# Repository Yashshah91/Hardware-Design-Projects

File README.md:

# 🔧 Electronics & Embedded Systems Projects  

Welcome to my collection of electronics, embedded systems, and power electronics projects.  
This repository contains hardware designs, schematics, and code implementations for robotics, microcontrollers, power supplies, and circuit testing solutions.  

---

## 📂 Project Index  

### 🤖 Robotics & Control  
- **[01_Robotics_Controller_4Axis](./01_Robotics_Controller_4Axis)**  
  A 4-axis robotics controller designed for precision motor control and automation tasks.  

### 🔬 Microcontroller Boards  
- **[02_ATmega128A_DevBoard](./02_ATmega128A_DevBoard)**  
  Custom development board based on the ATmega128A microcontroller for embedded applications.  

### ⚡ Power Electronics  
- **[03_Power_Solutions_Shared](./03_Power_Solutions_Shared)**  
  A collection of shared power solutions for multiple projects.  
- **[05_12V-10A-Power-Supply-Circuit](./05_12V-10A-Power-Supply-Circuit)**  
  A high-current regulated power supply circuit (12V, 10A).  
- **[06_Battery_Charger_and_Protection](./06_Battery_Charger_and_Protection)**  
  Battery charging and protection circuit ensuring safe operation for lithium-based batteries.  

### 🧪 Circuit Testers  
- **[04_555-Tester](./04_555-Tester)**  
  A tester circuit for the popular NE555 timer IC.  

---

## 🚀 Getting Started  

Each project folder contains:  
- ✅ Circuit diagrams / schematics  
- ✅ PCB layouts (if applicable)  
- ✅ Source code / firmware (for microcontroller-based designs)  
- ✅ Documentation & notes

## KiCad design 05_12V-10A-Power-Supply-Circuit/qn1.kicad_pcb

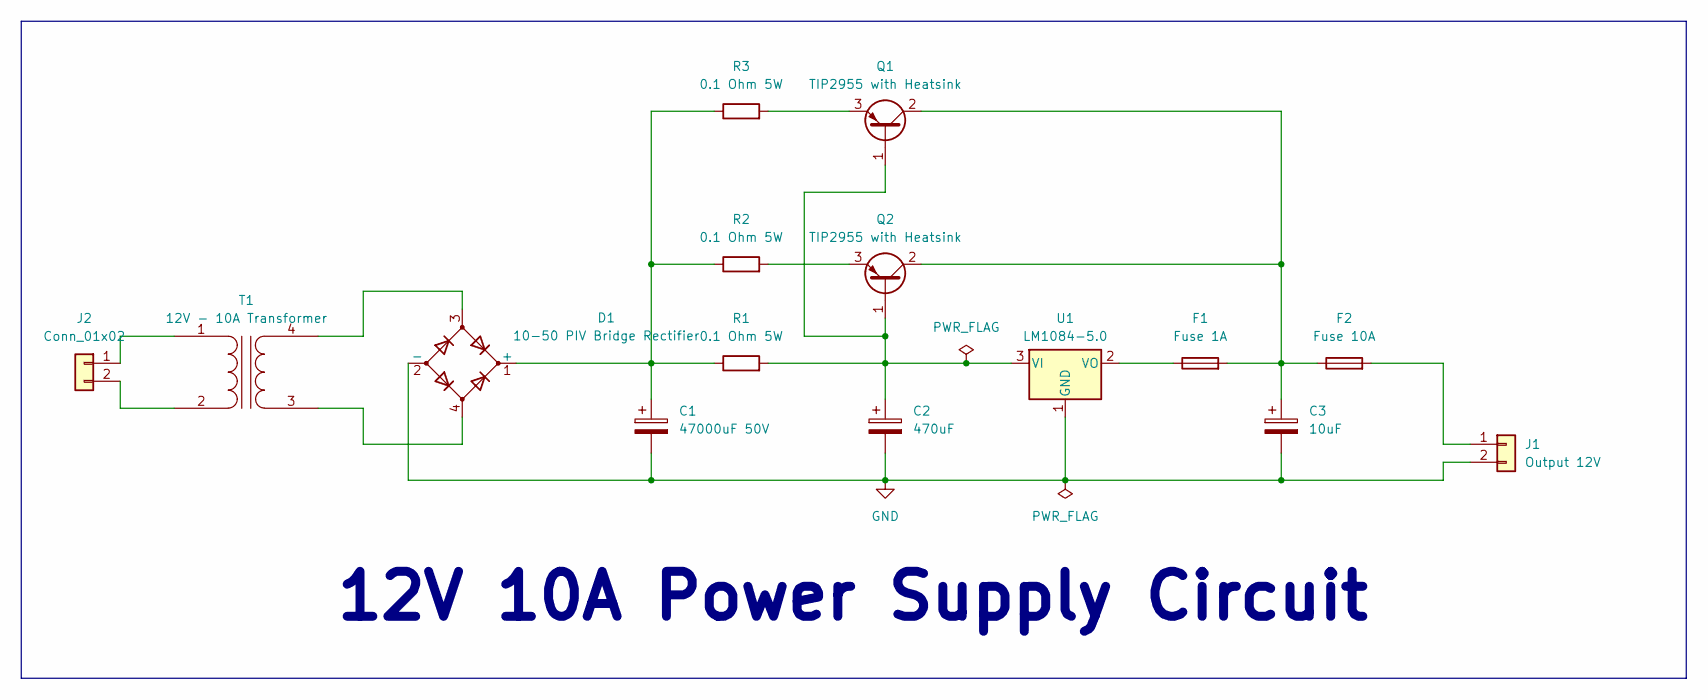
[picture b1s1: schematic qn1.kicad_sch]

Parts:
C1: 47000uF 50V; C_Radial_D16.0mm_H25.0mm_P7.50mm
C2: 470uF; C_Radial_D10.0mm_H12.5mm_P5.00mm
C3: 10uF; C_Radial_D5.0mm_H11.0mm_P2.00mm
D1: 10-50 PIV Bridge Rectifier; DIP-4_W7.62mm
F1: Fuse 1A; Fuse_BelFuse_0ZRE0150FF_L23.4mm_W5.3mm
F2: Fuse 10A; Fuse_BelFuse_0ZRE0150FF_L23.4mm_W5.3mm
J1: Output 12V; PinHeader_1x02_P2.54mm_Vertical
J2: Conn_01x02; PinHeader_1x02_P2.54mm_Vertical
Q1, Q2: TIP2955 with Heatsink; TO-218-3_Vertical
R1, R2, R3: 0.1 Ohm 5W; R_Axial_DIN0207_L6.3mm_D2.5mm_P7.62mm_Horizontal
T1: 12V - 10A Transformer; Transformer_CHK_EI54-12VA_1xSec
U1: LM1084-5.0; TO-220-3_Vertical

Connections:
GND: C1.2, C2.2, C3.2, D1.2 (-), J1.2, U1.1 (GND)
unnamed: C1.1, D1.1 (+), R1.1, R2.1, R3.1
unnamed: F2.2, J1.1
unnamed: J2.1, T1.1 (AA)
unnamed: J2.2, T1.2 (AB)
unnamed: C2.1, Q1.1 (B), Q2.1 (B), R1.2, U1.3 (VI)
unnamed: C3.1, F1.2, F2.1, Q1.2 (C), Q2.2 (C)
unnamed: Q1.3 (E), R3.2
unnamed: Q2.3 (E), R2.2
unnamed: D1.4, T1.3 (SA)
unnamed: D1.3, T1.4 (SB)
unnamed: F1.1, U1.2 (VO)

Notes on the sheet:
12V 10A Power Supply Circuit

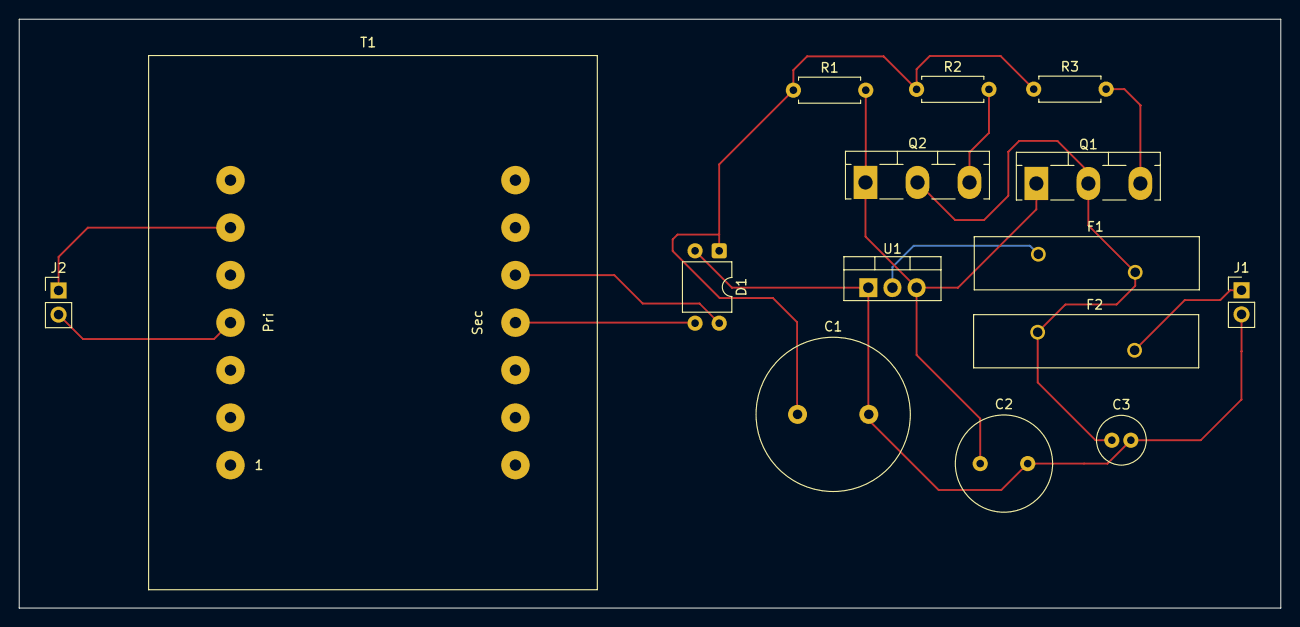
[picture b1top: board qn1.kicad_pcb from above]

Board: 2 copper layers, 132.8 x 62.0 mm, 15 parts (0 on the bottom side), 12 nets.

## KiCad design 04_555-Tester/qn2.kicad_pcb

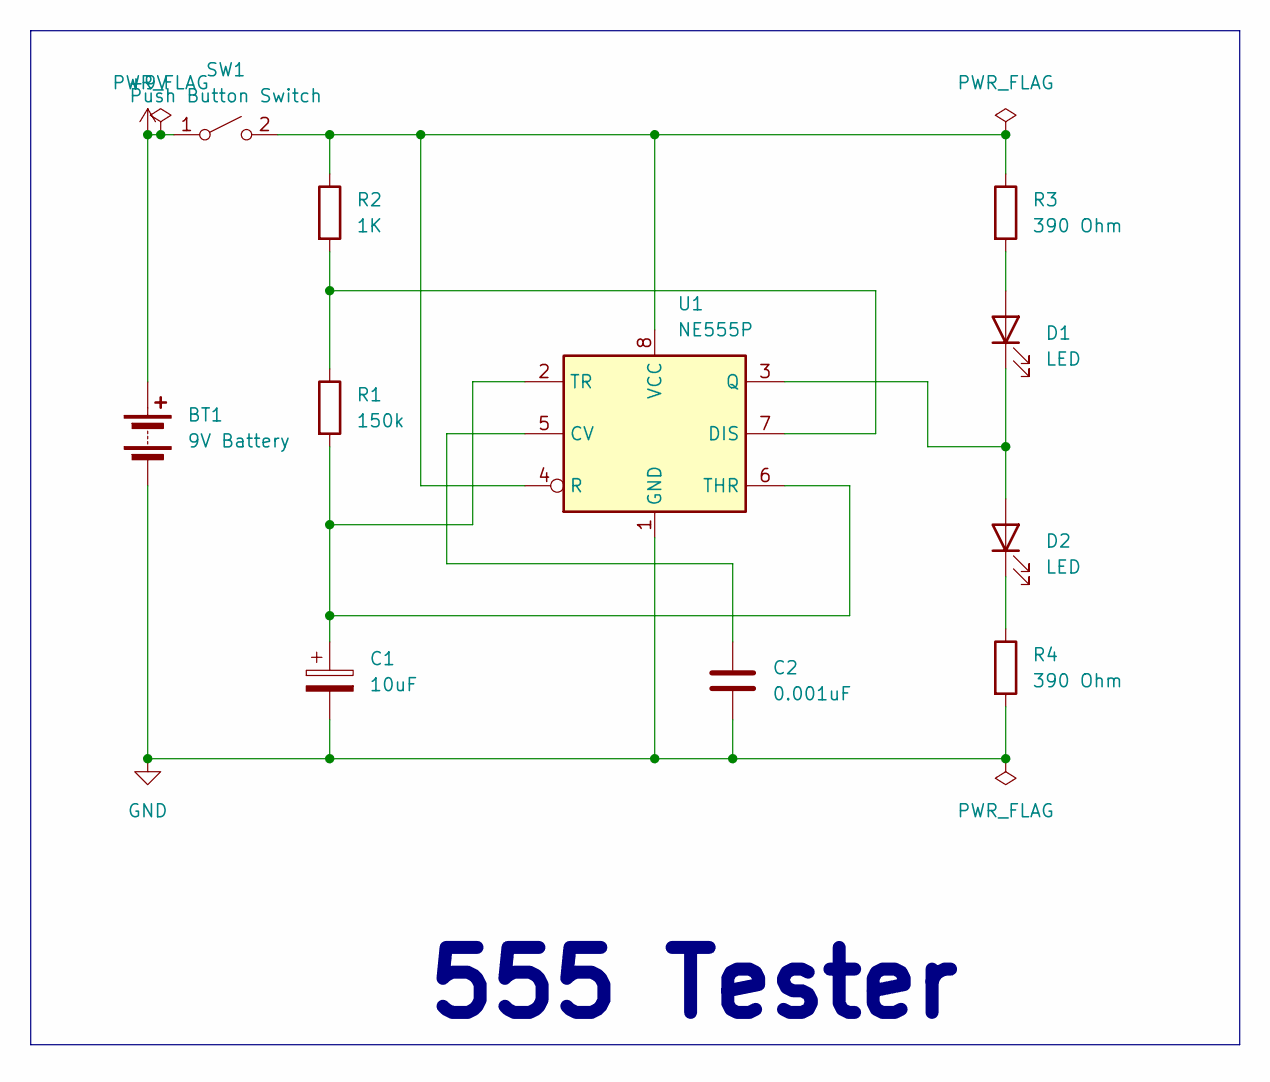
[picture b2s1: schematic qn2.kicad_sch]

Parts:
BT1: 9V Battery; BatteryHolder_Keystone_2462_2xAA
C1: 10uF; CP_Radial_D10.0mm_P7.50mm
C2: 0.001uF; CP_Axial_L10.0mm_D4.5mm_P15.00mm_Horizontal
D1, D2: LED; LED_D3.0mm
R1: 150k; R_Axial_DIN0207_L6.3mm_D2.5mm_P7.62mm_Horizontal
R2: 1K; R_Axial_DIN0207_L6.3mm_D2.5mm_P7.62mm_Horizontal
R3, R4: 390 Ohm; R_Axial_DIN0207_L6.3mm_D2.5mm_P7.62mm_Horizontal
SW1: Push Button Switch; SW_CW_GPTS203211B
U1: NE555P; DIP-8_W7.62mm

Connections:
+9V: BT1.1 (+), SW1.1 (A)
GND: BT1.2 (-), C1.2, C2.2, R4.2, U1.1 (GND)
unnamed: D1.2 (A), R3.2
unnamed: D1.1 (K), D2.2 (A), U1.3 (Q)
unnamed: D2.1 (K), R4.1
unnamed: R2.1, R3.1, SW1.2 (B), U1.4 (R), U1.8 (VCC)
unnamed: C2.1, U1.5 (CV)
unnamed: R1.1, R2.2, U1.7 (DIS)
unnamed: C1.1, R1.2, U1.2 (TR), U1.6 (THR)

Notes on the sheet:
555 Tester

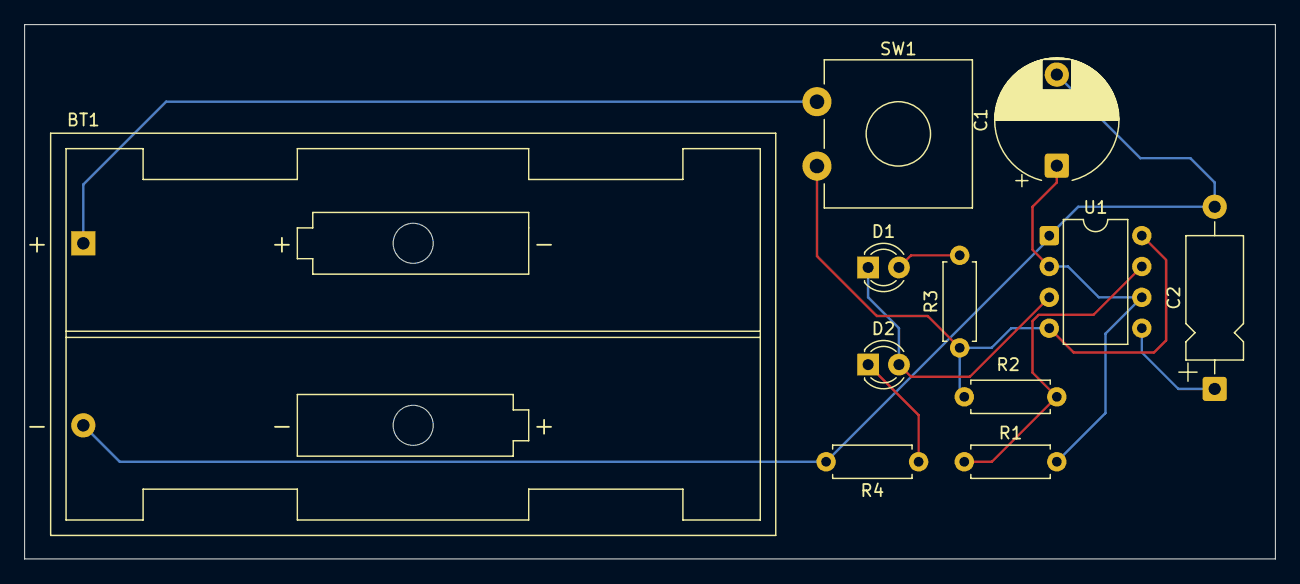
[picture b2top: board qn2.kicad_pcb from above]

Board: 2 copper layers, 103.0 x 44.0 mm, 11 parts (0 on the bottom side), 9 nets.

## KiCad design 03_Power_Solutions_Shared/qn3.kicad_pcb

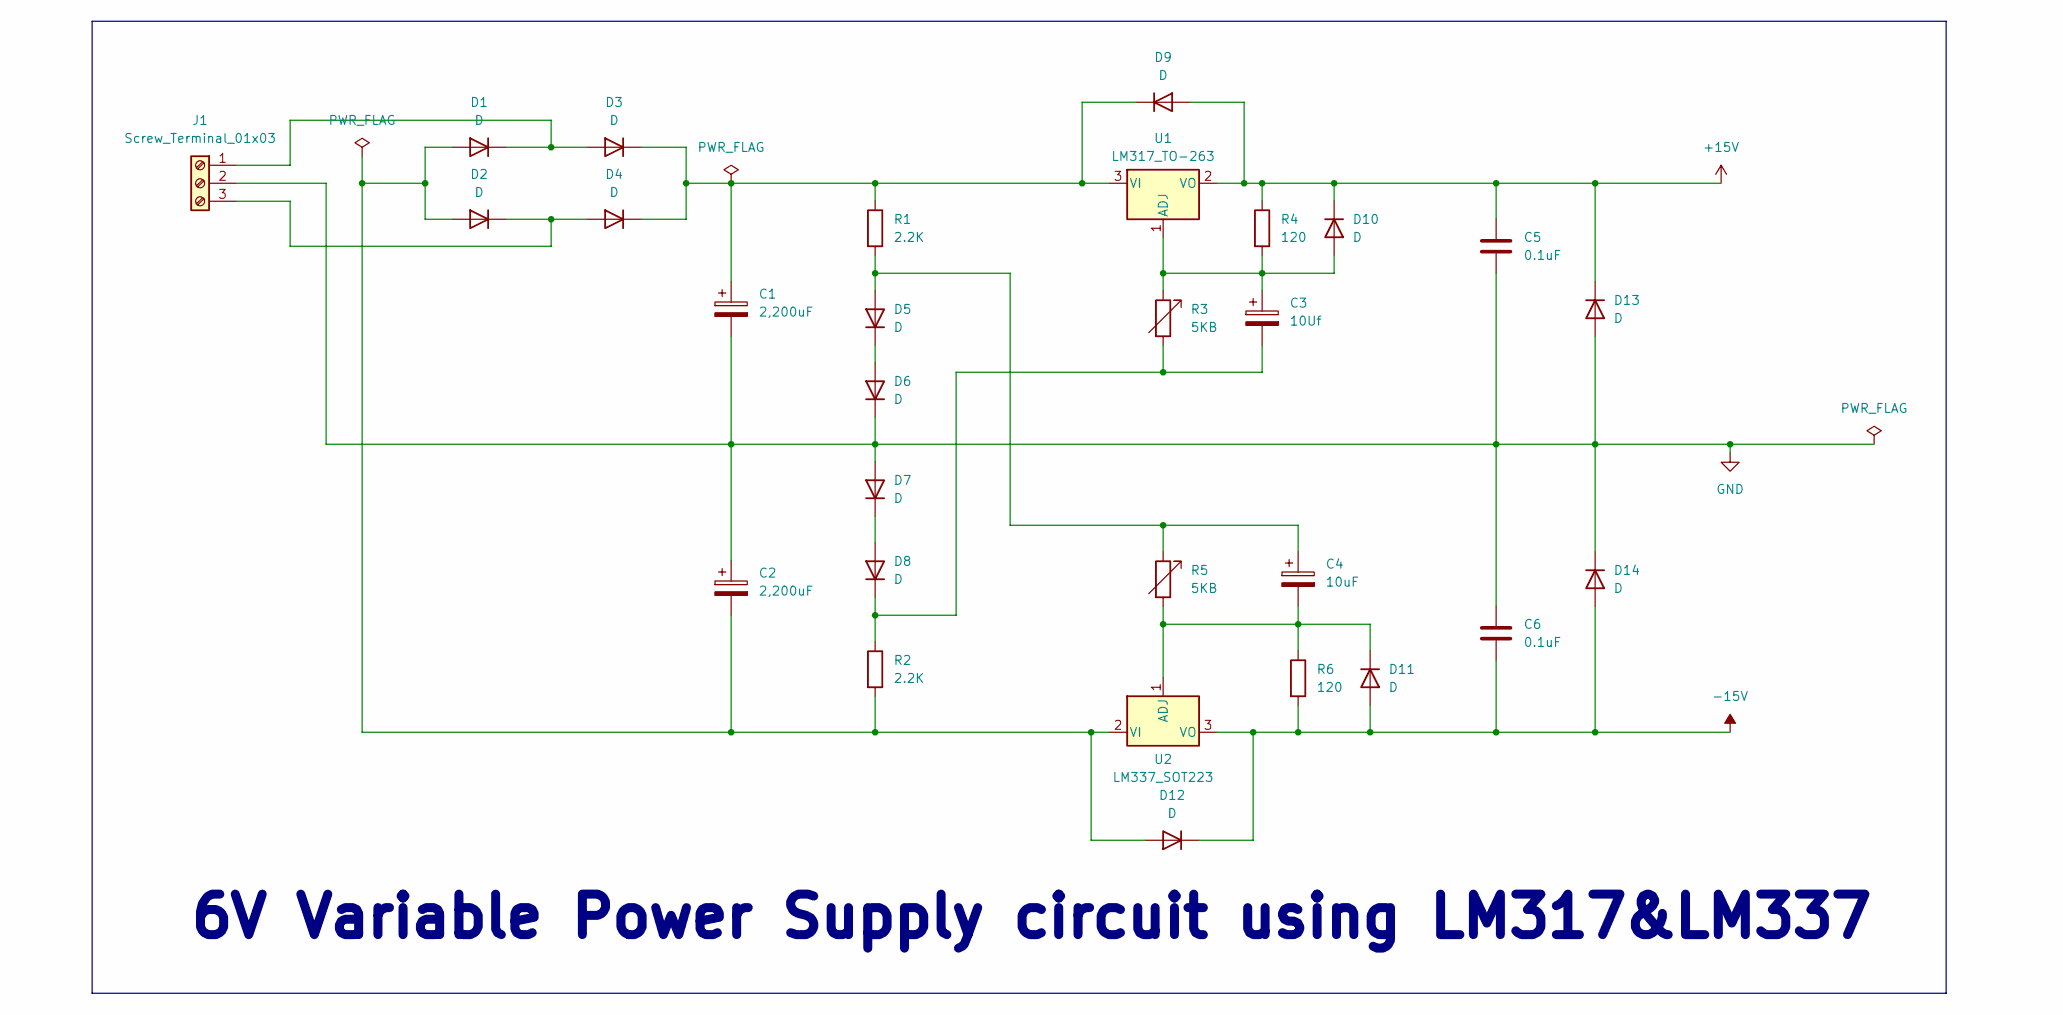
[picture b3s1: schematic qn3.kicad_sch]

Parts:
C1: 2,200uF; CP_Radial_D4.0mm_P2.00mm
C2: 2,200uF; CP_Radial_D5.0mm_P2.50mm
C3: 10Uf; CP_Radial_D4.0mm_P2.00mm
C4: 10uF; CP_Radial_D4.0mm_P2.00mm
C5, C6: 0.1uF; CP_Radial_D4.0mm_P2.00mm
D1, D2, D3, D4, D5, D6, D7, D8, D9, D10, D11, D12, D13, D14: D; D_DO-35_SOD27_P7.62mm_Horizontal
J1: Screw_Terminal_01x03; PinSocket_1x03_P2.54mm_Vertical
R1, R2: 2.2K; R_Axial_DIN0207_L6.3mm_D2.5mm_P10.16mm_Horizontal
R3, R5: 5KB; R_Axial_DIN0207_L6.3mm_D2.5mm_P10.16mm_Horizontal
R4, R6: 120; R_Axial_DIN0207_L6.3mm_D2.5mm_P10.16mm_Horizontal
U1: LM317_TO-263; TO-262-3_Vertical
U2: LM337_SOT223; TO-220F-3_Vertical

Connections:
+15V: C5.1, D9.2 (A), D10.1 (K), D13.1 (K), R4.1, U1.2 (VO)
-15V: C6.2, D11.2 (A), D12.1 (K), D14.2 (A), R6.2, U2.3 (VO)
GND: C1.2, C2.1, C5.2, C6.1, D6.1 (K), D7.2 (A), D13.2 (A), D14.1 (K), J1.2
unnamed: C2.2, D1.2 (A), D2.2 (A), D12.2 (A), R2.2, U2.2 (VI)
unnamed: D1.1 (K), D3.2 (A), J1.1
unnamed: D2.1 (K), D4.2 (A), J1.3
unnamed: C1.1, D3.1 (K), D4.1 (K), D9.1 (K), R1.1, U1.3 (VI)
unnamed: C4.1, D5.2 (A), R1.2, R5.1
unnamed: D5.1 (K), D6.2 (A)
unnamed: D7.1 (K), D8.2 (A)
unnamed: C3.2, D8.1 (K), R2.1, R3.2
unnamed: C3.1, D10.2 (A), R3.1, R4.2, U1.1 (ADJ)
unnamed: C4.2, D11.1 (K), R5.2, R6.1, U2.1 (ADJ)

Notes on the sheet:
6V Variable Power Supply circuit using LM317&LM337

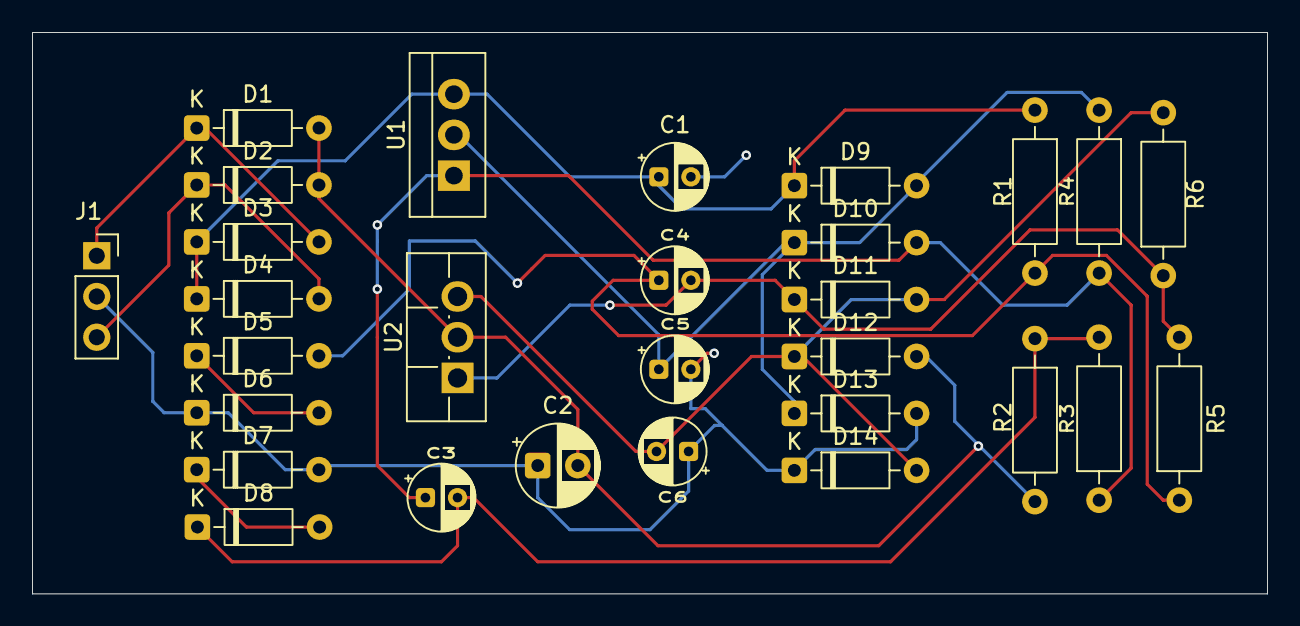
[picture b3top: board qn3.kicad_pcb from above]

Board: 2 copper layers, 77.0 x 35.0 mm, 29 parts (0 on the bottom side), 13 nets.

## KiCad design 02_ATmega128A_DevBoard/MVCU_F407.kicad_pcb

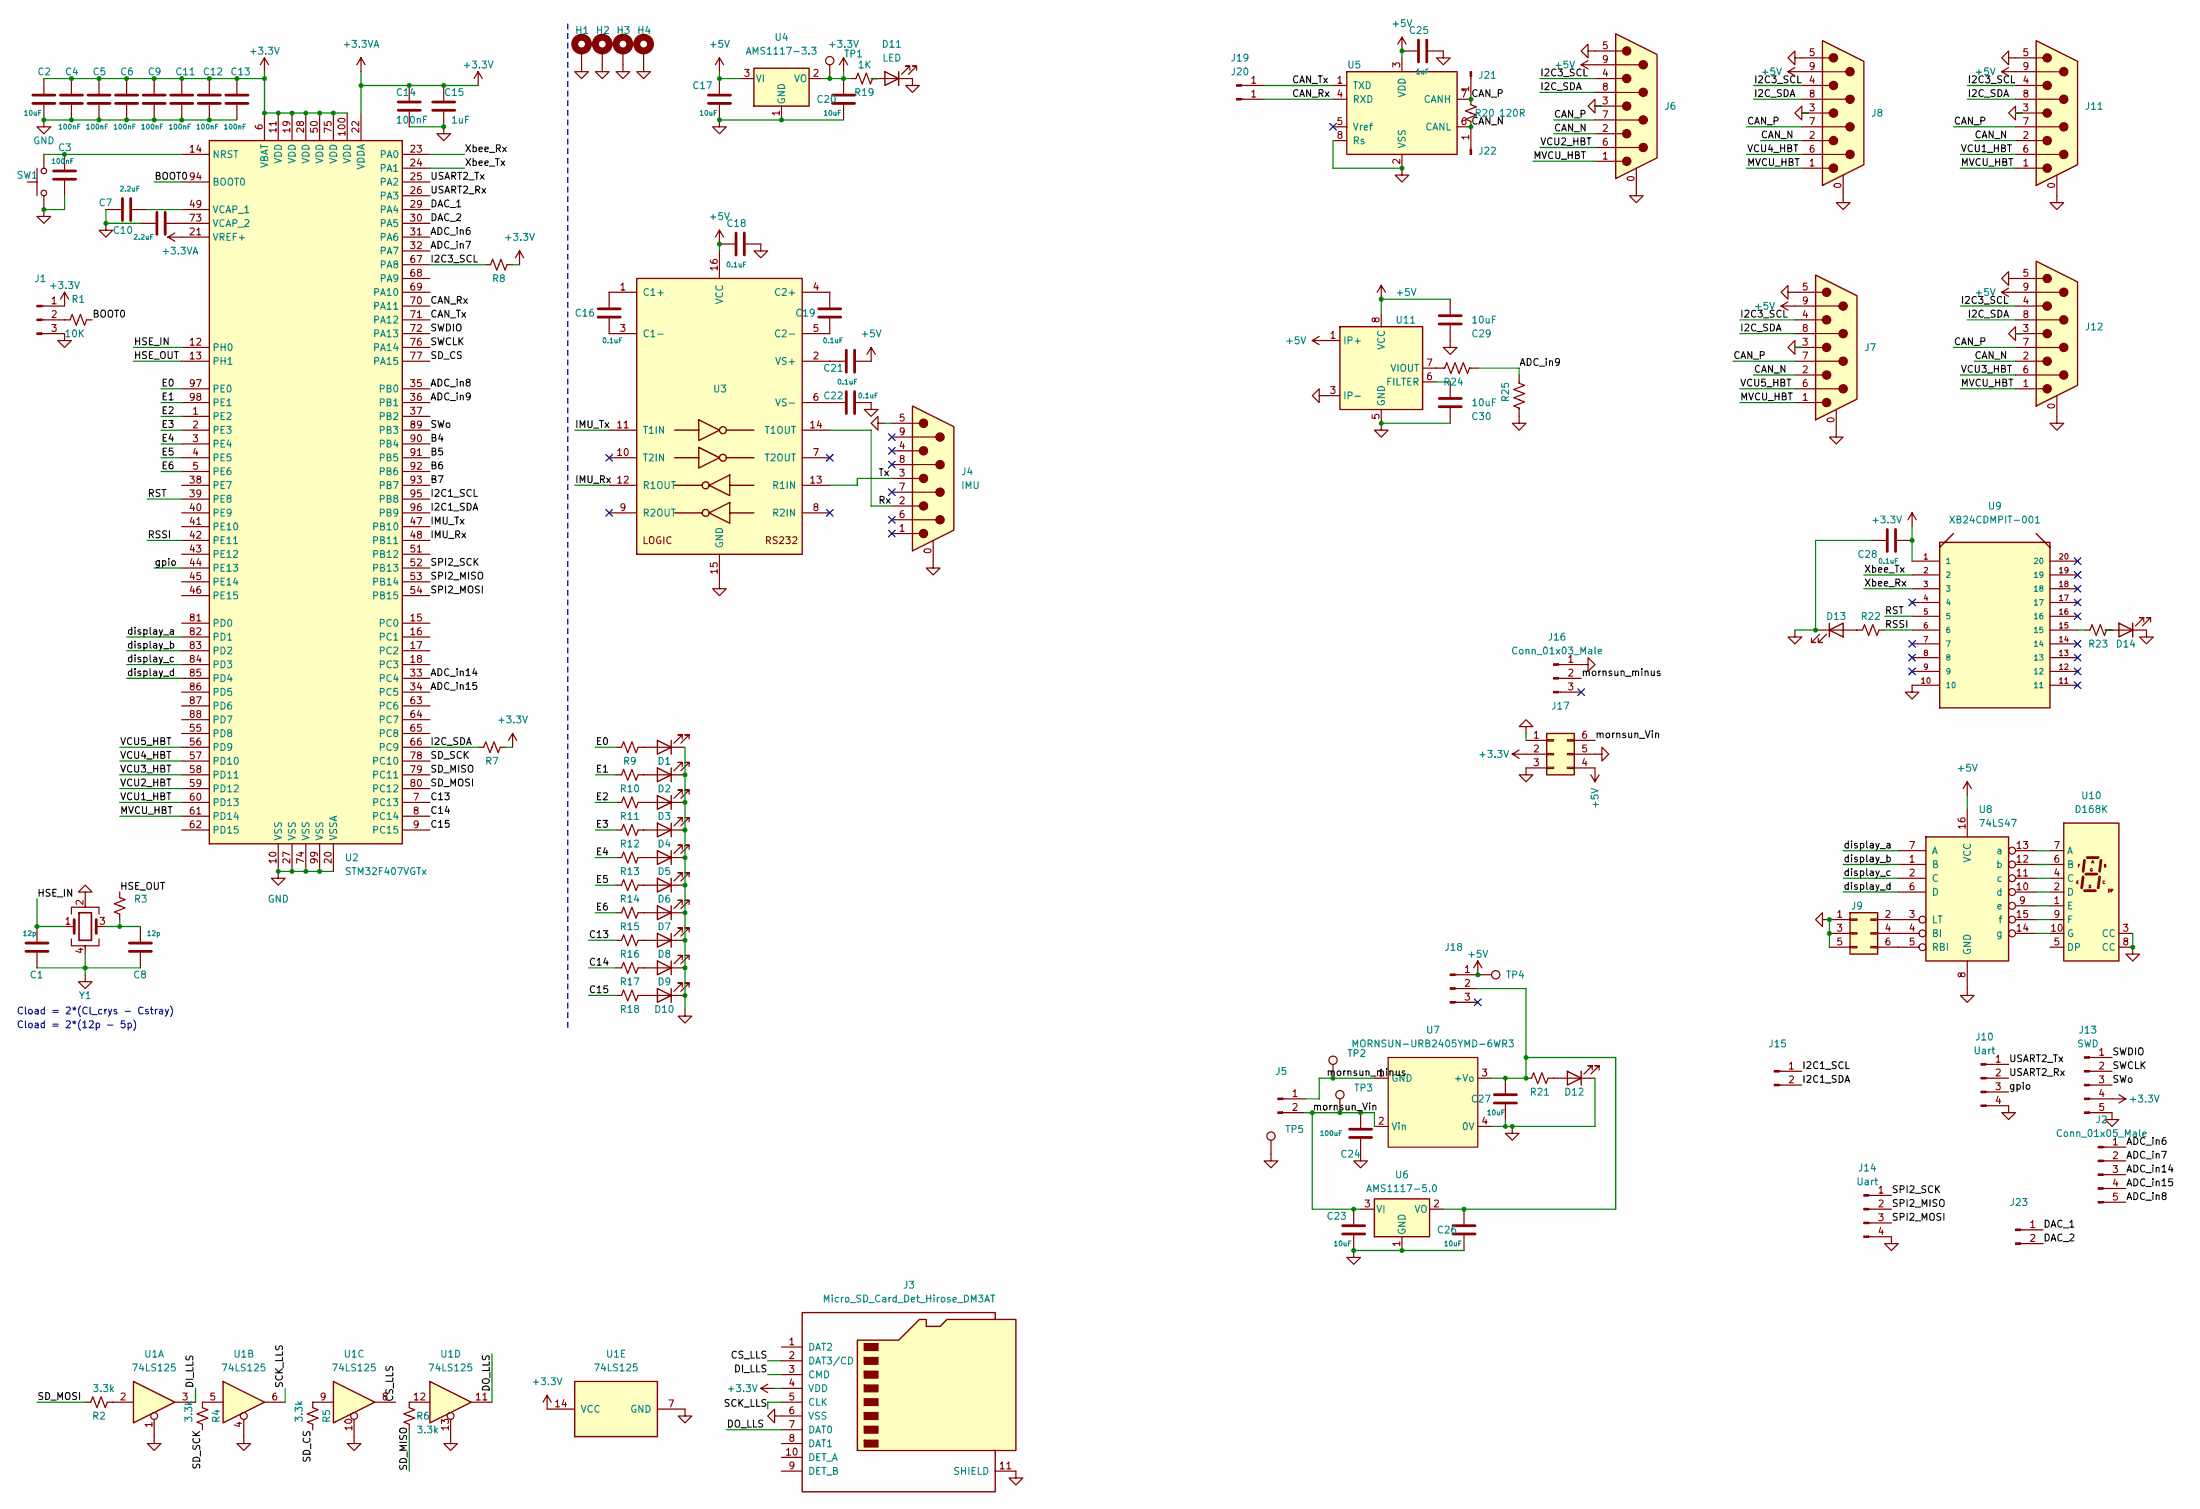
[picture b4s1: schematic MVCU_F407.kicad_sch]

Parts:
C1, C8: 12p; C_0805_2012Metric_Pad1.18x1.45mm_HandSolder
C2, C17, C20, C23, C26, C27, C29, C30: 10uF; C_0805_2012Metric_Pad1.18x1.45mm_HandSolder
C3, C4, C5, C6, C9, C11, C12, C13, C14: 100nF; C_0805_2012Metric_Pad1.18x1.45mm_HandSolder
C7, C10: 2.2uF; C_0805_2012Metric_Pad1.18x1.45mm_HandSolder
C15, C25: 1uF; C_0805_2012Metric_Pad1.18x1.45mm_HandSolder
C16, C18, C19, C21, C22, C28: 0.1uF; C_0805_2012Metric_Pad1.18x1.45mm_HandSolder
C24: 100uF; C_0805_2012Metric_Pad1.18x1.45mm_HandSolder
D1, D2, D3, D4, D5, D6, D7, D8, D9, D10, D11, D12, D13, D14: LED; LED_0805_2012Metric_Pad1.15x1.40mm_HandSolder
H1, H2, H3, H4: MountingHole_Pad; MountingHole_3.2mm_M3_DIN965_Pad
J1, J16, J18: Conn_01x03_Male; PinHeader_1x03_P2.54mm_Vertical
J2: Conn_01x05_Male; PinHeader_1x05_P2.54mm_Vertical
J3: Micro_SD_Card_Det_Hirose_DM3AT; microSD_HC_Hirose_DM3AT-SF-PEJM5
J4: IMU; DSUB-9_Male_Horizontal_P2.77x2.84mm_EdgePinOffset7.70mm_Hou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
J5: Conn_01x02_Male; PhoenixContact_MSTBA_2,5_2-G-5,08_1x02_P5.08mm_Horizontal
J6, J7, J8, J11, J12: DB9_Male_MountingHoles; DSUB-9_Male_Horizontal_P2.77x2.84mm_EdgePinOffset7.70mm_Hou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
J9: Conn_02x03_Odd_Even; PinSocket_1x06_P2.54mm_Vertical
J10, J14: Uart; PinHeader_1x04_P2.54mm_Vertical
J13: SWD; PinSocket_1x05_P2.54mm_Vertical
J15, J23: Conn_01x02_Male; PinHeader_1x02_P2.54mm_Vertical
J17: Conn_02x03_Counter_Clockwise; PinHeader_2x03_P2.54mm_Vertical
J19, J20, J21, J22: Conn_01x01_Male; PinHeader_1x01_P2.54mm_Vertical
R1: 10K; R_0805_2012Metric_Pad1.20x1.40mm_HandSolder
R2, R4, R5, R6: 3.3k; R_0805_2012Metric_Pad1.20x1.40mm_HandSolder
R3: R_Small_US; R_0805_2012Metric_Pad1.20x1.40mm_HandSolder
R7, R8, R9, R10, R11, R12, R13, R14, R15, R16, R17, R18, R19, R21, R22, R23: 1K; R_0805_2012Metric_Pad1.20x1.40mm_HandSolder
R20: 120R; R_0805_2012Metric_Pad1.20x1.40mm_HandSolder
R24, R25: 1.5k; R_0805_2012Metric_Pad1.20x1.40mm_HandSolder
SW1: SW_Push; SW_PUSH_6mm_H5mm
TP1, TP2, TP3, TP4, TP5: TestPoint; TestPoint_Keystone_5010-5014_Multipurpose
U1: 74LS125; DIP-14_W7.62mm
U2: STM32F407VGTx; LQFP-100_14x14mm_P0.5mm
U3: MAX232; DIP-16_W7.62mm_SMDSocket_SmallPads
U4: AMS1117-3.3; SOT-223-3_TabPin2
U5: MCP2551-I-SN; SOIC-8_3.9x4.9mm_P1.27mm
U6: AMS1117-5.0; SOT-223-3_TabPin2
U7: MORNSUN-URB2405YMD-6WR3
U8: 74LS47; DIP-16_W7.62mm
U9: XB24CDMPIT-001; XBEE
U10: D168K; D1X8K
U11: ACS712xLCTR-20A; SOIC-8_3.9x4.9mm_P1.27mm
Y1: Crystal_GND24; Crystal_SMD_3225-4Pin_3.2x2.5mm_HandSoldering

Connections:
+3.3V: C2.1, C4.1, C5.1, C6.1, C9.1, C11.1, C12.1, C13.1, C14.1, C15.1, C20.1, C28.1, J1.1, J3.4 (VDD), J13.4, J17.2, R7.1, R8.1, R19.2, TP1.1, U1.14 (VCC), U2.6 (VBAT), U2.11 (VDD), U2.19 (VDD), U2.21 (VREF+), U2.22 (VDDA), U2.28 (VDD), U2.50 (VDD), U2.75 (VDD), U2.100 (VDD), U4.2 (VO), U9.1; also elsewhere on the board
+5V: C17.1, C18.1, C21.1, C25.1, C29.1, J6.9, J7.9, J8.9, J11.9, J12.9, J17.4, J18.1, TP4.1, U3.16 (VCC), U4.3 (VI), U5.3 (VDD), U8.16 (VCC), U11.1 (IP+), U11.2 (IP+), U11.8 (VCC); also elsewhere on the board
/ADC_in6: J2.1, U2.31 (PA6)
/ADC_in7: J2.2, U2.32 (PA7)
/ADC_in8: J2.5, U2.35 (PB0)
/ADC_in9: R24.2, R25.1, U2.36 (PB1)
/ADC_in14: J2.3, U2.33 (PC4)
/ADC_in15: J2.4, U2.34 (PC5)
/B4: U2.90 (PB4)
/B5: U2.91 (PB5)
/B6: U2.92 (PB6)
/B7: U2.93 (PB7)
/BOOT0: R1.2, U2.94 (BOOT0)
/C13: R16.2, U2.7 (PC13)
/C14: R17.2, U2.8 (PC14)
/C15: R18.2, U2.9 (PC15)
/CAN_N: J6.2, J7.2, J8.2, J11.2, J12.2, J22.1, R20.2, U5.6 (CANL)
/CAN_P: J6.7, J7.7, J8.7, J11.7, J12.7, J21.1, R20.1, U5.7 (CANH)
/CAN_Rx: J20.1, U2.70 (PA11), U5.4 (RXD)
/CAN_Tx: J19.1, U2.71 (PA12), U5.1 (TXD)
/CS_LLS: J3.2 (DAT3/CD), U1.8
/DAC_1: J23.1, U2.29 (PA4)
/DAC_2: J23.2, U2.30 (PA5)
/DI_LLS: J3.3 (CMD), U1.3
/E0: R9.2, U2.97 (PE0)
/E1: R10.2, U2.98 (PE1)
/E2: R11.2, U2.1 (PE2)
/E3: R12.2, U2.2 (PE3)
/E4: R13.2, U2.3 (PE4)
/E5: R14.2, U2.4 (PE5)
/E6: R15.2, U2.5 (PE6)
/HSE_IN: C1.2, U2.12 (PH0), Y1.1
/HSE_OUT: R3.1, U2.13 (PH1)
/I2C1_SCL: J15.1, U2.95 (PB8)
/I2C1_SDA: J15.2, U2.96 (PB9)
/I2C3_SCL: J6.4, J7.4, J8.4, J11.4, J12.4, R8.2, U2.67 (PA8)
/I2C_SDA: J6.8, J7.8, J8.8, J11.8, J12.8, R7.2, U2.66 (PC9)
/IMU_Rx: U2.48 (PB11), U3.12 (R1OUT)
/IMU_Tx: U2.47 (PB10), U3.11 (T1IN)
/MVCU_HBT: J6.1, J7.1, J8.1, J11.1, J12.1, U2.61 (PD14)
/RSSI: R22.2, U2.42 (PE11), U9.6
/RST: U2.39 (PE8), U9.5
/Rx: J4.2, U3.14 (T1OUT)
/SCK_LLS: J3.5 (CLK), U1.6
/SD_CS: R5.2, U2.77 (PA15)
/SD_MOSI: R2.2, U2.80 (PC12)
/SD_SCK: R4.2, U2.78 (PC10)
/SPI2_MISO: J14.2, U2.53 (PB14)
/SPI2_MOSI: J14.3, U2.54 (PB15)
/SPI2_SCK: J14.1, U2.52 (PB13)
/SWCLK: J13.2, U2.76 (PA14)
/SWDIO: J13.1, U2.72 (PA13)
/SWo: J13.3, U2.89 (PB3)
/Tx: J4.3, U3.13 (R1IN)
/USART2_Rx: J10.2, U2.26 (PA3)
/USART2_Tx: J10.1, U2.25 (PA2)
/VCU1_HBT: J11.6, U2.60 (PD13)
/VCU2_HBT: J6.6, U2.59 (PD12)
/VCU3_HBT: J12.6, U2.58 (PD11)
/VCU4_HBT: J8.6, U2.57 (PD10)
/VCU5_HBT: J7.6, U2.56 (PD9)
/Xbee_Rx: U2.23 (PA0), U9.3
/Xbee_Tx: U2.24 (PA1), U9.2
/display_a: U2.82 (PD1), U8.7 (A)
/display_b: U2.83 (PD2), U8.1 (B)
/display_c: U2.84 (PD3), U8.2 (C)
/display_d: U2.85 (PD4), U8.6 (D)
/gpio: J10.3, U2.44 (PE13)
/mornsun_Vin: C23.1, C24.1, J5.2, J17.6, TP3.1, U6.3 (VI), U7.2 (Vin); also elsewhere on the board
/mornsun_minus: J5.1, J16.2, TP2.1, U7.1 (GND); also elsewhere on the board
GND: C1.1, C2.2, C3.2, C4.2, C5.2, C6.2, C7.1, C8.1, C9.2, C10.1, C11.2, C12.2, C13.2, C14.2, C15.2, C17.2, C18.2, C20.2, C22.1, C23.2, C24.2, C25.2, C26.2, C27.1, C28.2, C29.2, C30.2, D1.1 (K), D2.1 (K), D3.1 (K), D4.1 (K), D5.1 (K), D6.1 (K), D7.1 (K), D8.1 (K), D9.1 (K), D10.1 (K), D11.1 (K), D12.1 (K), D13.1 (K), D14.1 (K), H1.1, H2.1, H3.1, H4.1, J1.3, J3.6 (VSS), J3.11 (SHIELD), J4.0 (PAD), J4.5, J6.0 (PAD), J6.3, J6.5, J7.0 (PAD), J7.3, J7.5, J8.0 (PAD), J8.3, J8.5, J9.1, J9.3, J9.5, J10.4, J11.0 (PAD), J11.3, J11.5, J12.0 (PAD), J12.3, J12.5, J13.5, J14.4, J16.1, J17.1, J17.3, J17.5, R25.2, SW1.1, TP5.1, U1.1, U1.4, U1.7 (GND), U1.10, U1.13, U2.10 (VSS), U2.20 (VSSA), U2.27 (VSS), U2.74 (VSS), U2.99 (VSS), U3.15 (GND), U4.1 (GND), U5.2 (VSS), U5.8 (Rs), U6.1 (GND), U7.4 (0V), U8.8 (GND), U9.10, U10.3 (CC), U10.8 (CC), U11.3 (IP-), U11.4 (IP-), U11.5 (GND), Y1.2, Y1.4; also elsewhere on the board
unnamed: C3.1, SW1.2, U2.14 (NRST)
unnamed: C7.2, U2.49 (VCAP_1)
unnamed: C8.2, R3.2, Y1.3
unnamed: C10.2, U2.73 (VCAP_2)
unnamed: C16.1, U3.3 (C1-)
unnamed: C16.2, U3.1 (C1+)
unnamed: C19.1, U3.5 (C2-)
unnamed: C19.2, U3.4 (C2+)
unnamed: C21.2, U3.2 (VS+)
unnamed: C22.2, U3.6 (VS-)
unnamed: C26.1, C27.2, J18.2, R21.2, U6.2 (VO), U7.3 (+Vo)
unnamed: C30.1, U11.6 (FILTER)
unnamed: D1.2 (A), R9.1
unnamed: D2.2 (A), R10.1
unnamed: D3.2 (A), R11.1
unnamed: D4.2 (A), R12.1
unnamed: D5.2 (A), R13.1
unnamed: D6.2 (A), R14.1
unnamed: D7.2 (A), R15.1
unnamed: D8.2 (A), R16.1
unnamed: D9.2 (A), R17.1
unnamed: D10.2 (A), R18.1
unnamed: D11.2 (A), R19.1
unnamed: D12.2 (A), R21.1
unnamed: D13.2 (A), R22.1
unnamed: D14.2 (A), R23.1
unnamed: J1.2, R1.1
unnamed: J9.2, U8.3 (LT)
unnamed: J9.4, U8.4 (BI)
unnamed: J9.6, U8.5 (RBI)
unnamed: R2.1, U1.2
unnamed: R4.1, U1.5
unnamed: R5.1, U1.9
unnamed: R6.1, U1.12
unnamed: R23.2, U9.15
unnamed: R24.1, U11.7 (VIOUT)
unnamed: U8.9 (e), U10.1 (E)
unnamed: U8.10 (d), U10.2 (D)
unnamed: U8.11 (c), U10.4 (C)
unnamed: U8.12 (b), U10.6 (B)
unnamed: U8.13 (a), U10.7 (A)
unnamed: U8.15 (f), U10.9 (F)
unnamed: U8.14 (g), U10.10 (G)

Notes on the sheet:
Cload = 2*(12p - 5p)
Cload = 2*(Cl_crys - Cstray)

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
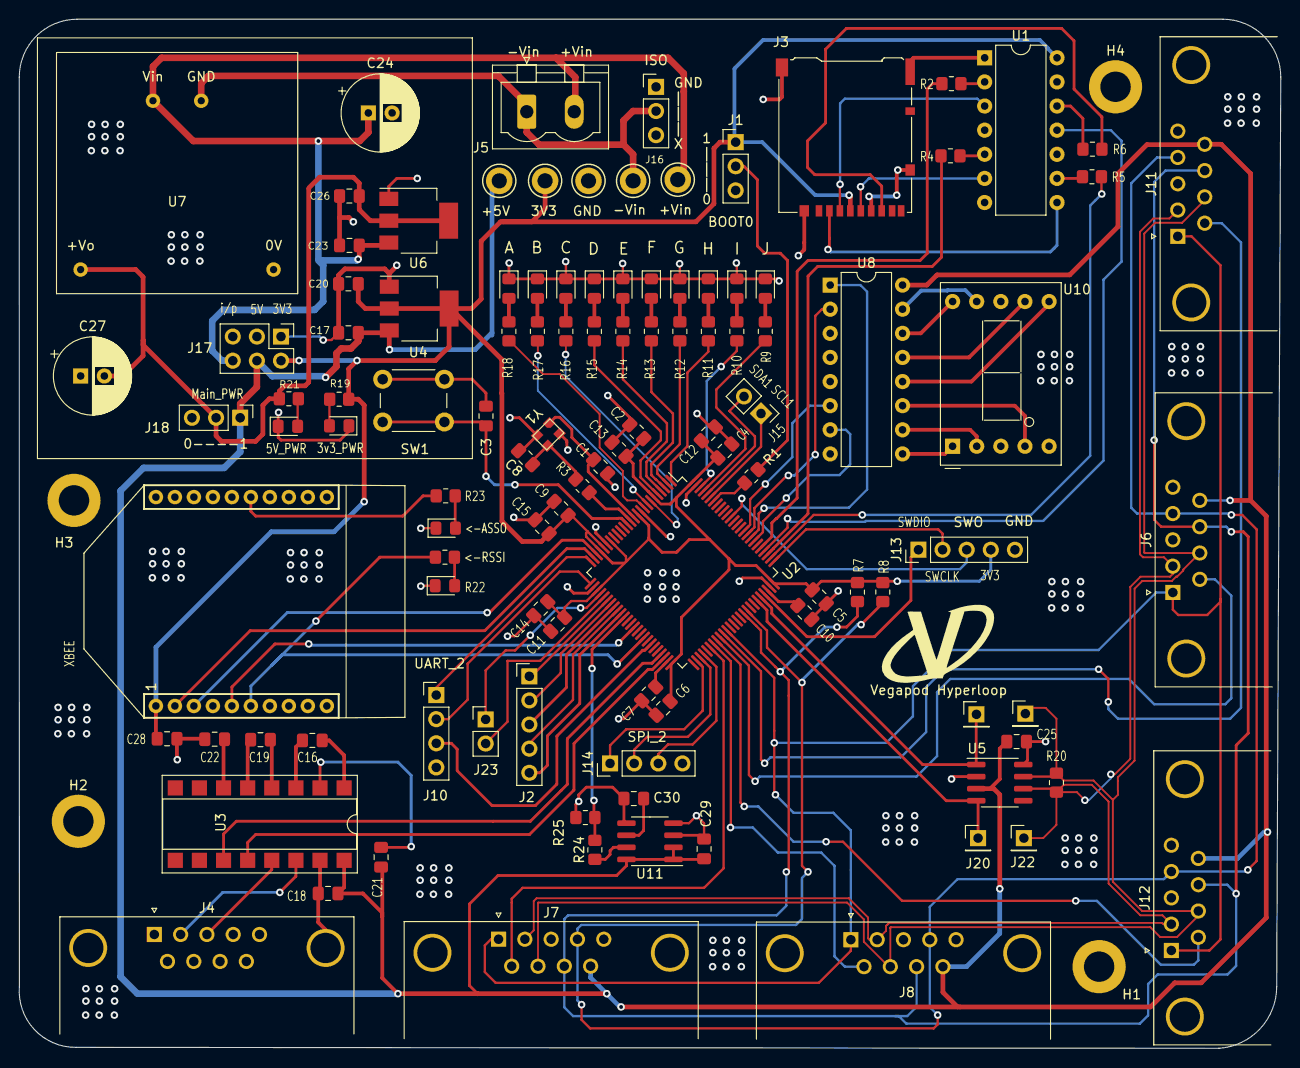
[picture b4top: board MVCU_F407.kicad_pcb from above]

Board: 4 copper layers, 132.8 x 108.4 mm, 113 parts (0 on the bottom side), 109 nets.

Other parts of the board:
3V3: TestPoint; TestPoint_Keystone_5010-5014_Multipurpose
+5V: TestPoint; TestPoint_Keystone_5010-5014_Multipurpose
+Vin: TestPoint; TestPoint_Keystone_5010-5014_Multipurpose
-Vin: TestPoint; TestPoint_Keystone_5010-5014_Multipurpose
GND: TestPoint; TestPoint_Keystone_5010-5014_Multipurpose

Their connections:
+3.3V: 3V3.1; also elsewhere on the board
+5V: +5V.1; also elsewhere on the board
/mornsun_Vin: +Vin.1; also elsewhere on the board
/mornsun_minus: -Vin.1; also elsewhere on the board
GND: GND.1; also elsewhere on the board

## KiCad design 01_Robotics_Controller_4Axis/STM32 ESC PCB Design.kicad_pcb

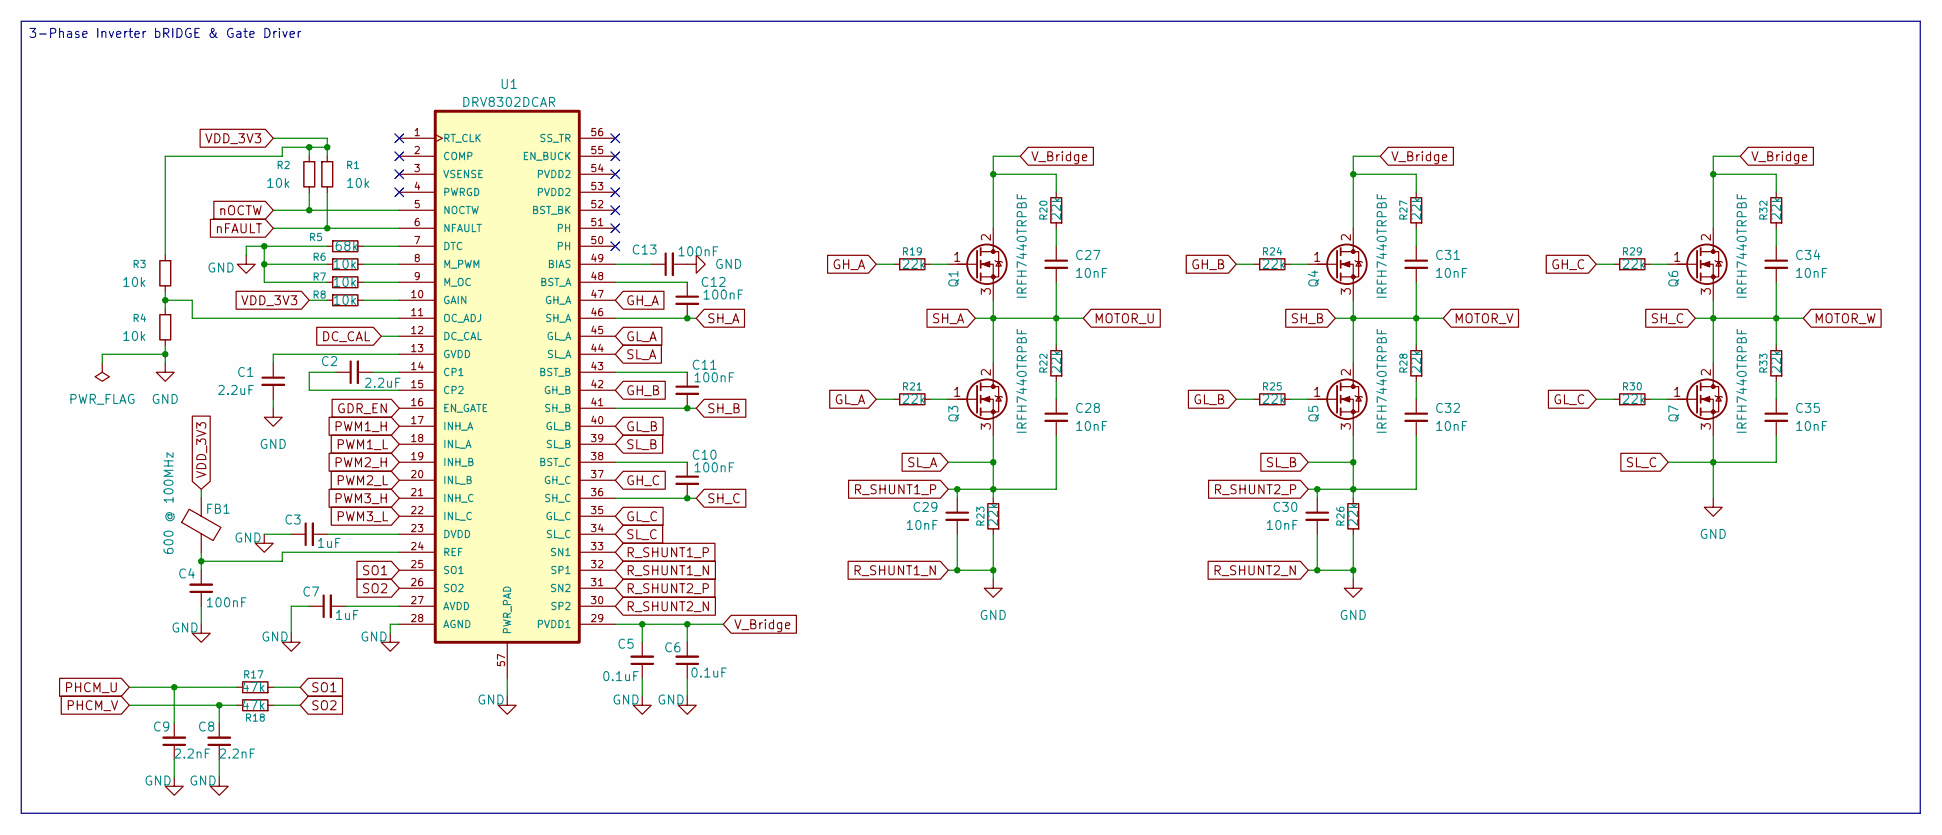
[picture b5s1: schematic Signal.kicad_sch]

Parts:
C1, C2: 2.2uF; C_Elec_3x5.4
C3, C7: 1uF; C_Elec_3x5.4
C4, C10, C11, C12, C13: 100nF; C_Elec_3x5.4
C5, C6: 0.1uF; C_Elec_3x5.4
C8, C9: 2.2nF; C_Elec_3x5.4
C27, C28, C29, C30, C31, C32, C34, C35: 10nF; C_Elec_3x5.4
FB1: 600 @ 100MHz; R_0603_1608Metric
Q1, Q3, Q4, Q5, Q6, Q7: IRFH7440TRPBF; TO-220-3_Vertical
R1, R2, R3, R4, R6, R7, R8: 10k; R_0805_2012Metric
R5: 68k; R_0805_2012Metric
R17, R18: 47k; R_0805_2012Metric
R19, R20, R21, R22, R23, R24, R25, R26, R27, R28, R29, R30, R32, R33: 22k; R_0805_2012Metric
U1: DRV8302DCAR; SOP50P810X120-57N

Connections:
DC_CAL: U1.12 (DC_CAL); also elsewhere on the board
GDR_EN: U1.16 (EN_GATE); also elsewhere on the board
GH_A: R19.1, U1.47 (GH_A)
GH_B: R24.1, U1.42 (GH_B)
GH_C: R29.1, U1.37 (GH_C)
GL_A: R21.1, U1.45 (GL_A)
GL_B: R25.1, U1.40 (GL_B)
GL_C: R30.1, U1.35 (GL_C)
MOTOR_U: C12.2, C27.2, Q1.3 (S), Q3.2 (D), R22.2, U1.46 (SH_A)
MOTOR_V: C11.2, C31.2, Q4.3 (S), Q5.2 (D), R28.2, U1.41 (SH_B)
MOTOR_W: C10.2, C34.2, Q6.3 (S), Q7.2 (D), R33.2, U1.36 (SH_C)
unnamed: C27.1, R20.1
unnamed: C28.1, R22.1
unnamed: C31.1, R27.1
unnamed: C32.1, R28.1
unnamed: C34.1, R32.1
unnamed: C35.1, R33.1
unnamed: Q1.1 (G), R19.2
unnamed: Q3.1 (G), R21.2
unnamed: Q4.1 (G), R24.2
unnamed: Q5.1 (G), R25.2
unnamed: Q6.1 (G), R29.2
unnamed: Q7.1 (G), R30.2
unnamed: C7.2, U1.27 (AVDD)
unnamed: C13.1, U1.49 (BIAS)
unnamed: C12.1, U1.48 (BST_A)
unnamed: C11.1, U1.43 (BST_B)
unnamed: C10.1, U1.38 (BST_C)
unnamed: C2.2, U1.14 (CP1)
unnamed: C2.1, U1.15 (CP2)
unnamed: R5.2, U1.7 (DTC)
unnamed: C3.2, U1.23 (DVDD)
unnamed: R8.2, U1.10 (GAIN)
unnamed: C1.1, U1.13 (GVDD)
unnamed: R7.2, U1.9 (M_OC)
unnamed: R6.2, U1.8 (M_PWM)
unnamed: R3.2, R4.1, U1.11 (OC_ADJ)
unnamed: C4.2, FB1.2, U1.24 (REF)
PHCM_U: C9.2, R17.2; also elsewhere on the board
PHCM_V: C8.2, R18.2; also elsewhere on the board
PWM1_H: U1.17 (INH_A); also elsewhere on the board
PWM1_L: U1.18 (INL_A); also elsewhere on the board
PWM2_H: U1.19 (INH_B); also elsewhere on the board
PWM2_L: U1.20 (INL_B); also elsewhere on the board
PWM3_H: U1.21 (INH_C); also elsewhere on the board
PWM3_L: U1.22 (INL_C); also elsewhere on the board
R_SHUNT1_N: C1.2, C3.1, C4.1, C5.1, C6.1, C7.1, C8.1, C9.1, C13.2, C29.2, C30.2, C35.2, Q7.3 (S), R4.2, R5.1, R6.1, R7.1, R23.1, R26.1, U1.28 (AGND), U1.30 (SP2), U1.32 (SP1), U1.34 (SL_C), U1.57 (PWR_PAD); also elsewhere on the board
R_SHUNT1_P: C28.2, C29.1, Q3.3 (S), R23.2, U1.33 (SN1), U1.44 (SL_A)
R_SHUNT2_P: C30.1, C32.2, Q5.3 (S), R26.2, U1.31 (SN2), U1.39 (SL_B)
SO1: R17.1, U1.25 (SO1)
SO2: R18.1, U1.26 (SO2)
VDD_3V3: FB1.1, R1.1, R2.1, R3.1, R8.1; also elsewhere on the board
V_Bridge: C5.2, C6.2, Q1.2 (D), Q4.2 (D), Q6.2 (D), R20.2, R27.2, R32.2, U1.29 (PVDD1); also elsewhere on the board
nFAULT: R1.2, U1.6 (NFAULT); also elsewhere on the board
nOCTW: R2.2, U1.5 (NOCTW); also elsewhere on the board

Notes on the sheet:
3-Phase Inverter bRIDGE & Gate Driver
